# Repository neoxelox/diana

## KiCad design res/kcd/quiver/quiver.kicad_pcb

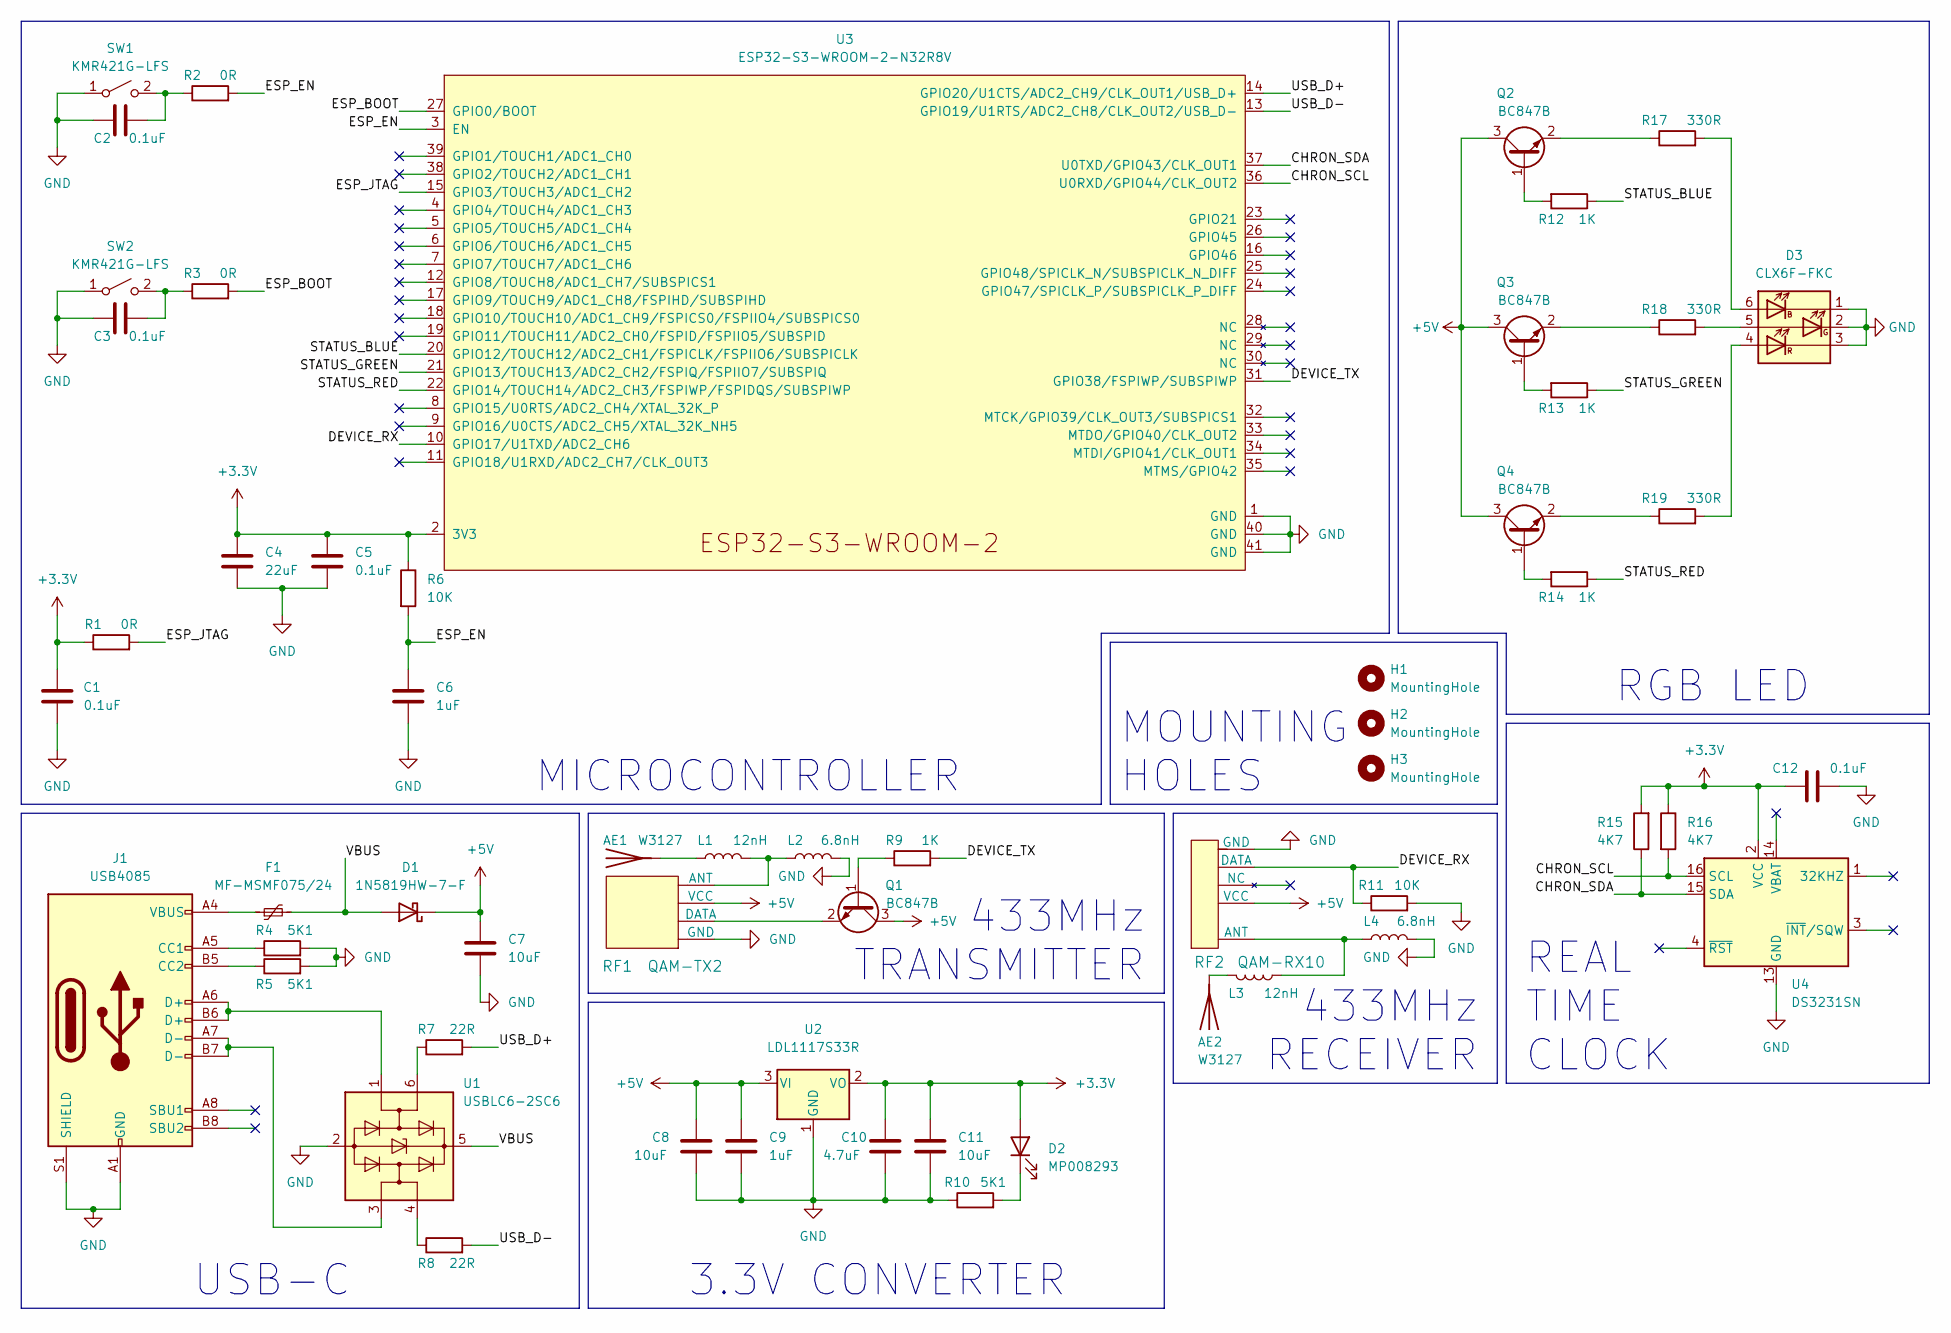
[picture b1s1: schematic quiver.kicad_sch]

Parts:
AE1, AE2: W3127
C1, C2, C3, C5, C12: 0.1uF; C_0805_2012Metric
C4: 22uF; C_0805_2012Metric
C6, C9: 1uF; C_0805_2012Metric
C7, C8, C11: 10uF; C_0805_2012Metric
C10: 4.7uF; C_0805_2012Metric
D1: 1N5819HW-7-F; D_SOD-123
D2: MP008293; LED_0805_2012Metric
D3: CLX6F-FKC
F1: MF-MSMF075/24; MF-MSMF075-24
H1, H2, H3: MountingHole; MountingHole_2.2mm_M2
J1: USB4085; GCT_USB4085
L1, L3: 12nH; L_0805_2012Metric
L2, L4: 6.8nH; L_0805_2012Metric
Q1, Q2, Q3, Q4: BC847B; SOT-23
R1, R2, R3: 0R; R_0805_2012Metric
R4, R5, R10: 5K1; R_0805_2012Metric
R6, R11: 10K; R_0805_2012Metric
R7, R8: 22R; R_0805_2012Metric
R9, R12, R13, R14: 1K; R_0805_2012Metric
R15, R16: 4K7; R_0805_2012Metric
R17, R18, R19: 330R; R_0805_2012Metric
RF1: QAM-TX2
RF2: QAM-RX10
SW1, SW2: KMR421G-LFS
U1: USBLC6-2SC6; SOT-23-6
U2: LDL1117S33R; SOT-223-3_TabPin2
U3: ESP32-S3-WROOM-2-N32R8V; ESP32-S3-WROOM-2
U4: DS3231SN; SOIC-16W_7.5x10.3mm_P1.27mm

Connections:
+3.3V: C1.2, C4.1, C5.1, C10.1, C11.1, C12.1, D2.2 (A), R1.1, R6.1, R15.2, R16.1, U2.2 (VO), U3.2 (3V3), U4.2 (VCC)
+5V: C7.1, C8.1, C9.1, D1.1 (K), Q1.3 (C), Q2.3 (C), Q3.3 (C), Q4.3 (C), RF1.3 (VCC), RF2.1 (VCC), U2.3 (VI)
/CHRON_SCL: R16.2, U3.36 (U0RXD/GPIO44/CLK_OUT2), U4.16 (SCL)
/CHRON_SDA: R15.1, U3.37 (U0TXD/GPIO43/CLK_OUT1), U4.15 (SDA)
/DEVICE_RX: R11.1, RF2.3 (DATA), U3.10 (GPIO17/U1TXD/ADC2_CH6)
/DEVICE_TX: R9.2, U3.31 (GPIO38/FSPIWP/SUBSPIWP)
/ESP_BOOT: R3.2, U3.27 (GPIO0/BOOT)
/ESP_EN: C6.1, R2.2, R6.2, U3.3 (EN)
/ESP_JTAG: R1.2, U3.15 (GPIO3/TOUCH3/ADC1_CH2)
/STATUS_BLUE: R12.1, U3.20 (GPIO12/TOUCH12/ADC2_CH1/FSPICLK/FSPIIO6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)
/STATUS_GREEN: R13.1, U3.21 (GPIO13/TOUCH13/ADC2_CH2/FSPIQ/FSPIIO7/S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)
/STATUS_RED: R14.1, U3.22 (GPIO14/TOUCH14/ADC2_CH3/FSPIWP/FSPIDQS/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)
/USB_D+: R7.2, U3.14 (GPIO20/U1CTS/ADC2_CH9/CLK_OUT1/USB_D+)
/USB_D-: R8.2, U3.13 (GPIO19/U1RTS/ADC2_CH8/CLK_OUT2/USB_D-)
/VBUS: D1.2 (A), F1.2, U1.5 (VBUS)
GND: C1.1, C2.1, C3.1, C4.2, C5.2, C6.2, C7.2, C8.2, C9.2, C10.2, C11.2, C12.2, D3.1 (BC), D3.2 (GC), D3.3 (RC), J1.A1 (GND), J1.A12 (GND), J1.B1 (GND), J1.B12 (GND), J1.S1 (SHIELD), L2.2, L4.2, R4.2, R5.2, R10.1, R11.2, RF1.1 (GND), RF2.4 (GND), SW1.1 (A), SW2.1 (A), U1.2 (GND), U2.1 (GND), U3.1 (GND), U3.40 (GND), U3.41 (GND), U4.5 (GND), U4.6 (GND), U4.7 (GND), U4.8 (GND), U4.9 (GND), U4.10 (GND), U4.11 (GND), U4.12 (GND), U4.13 (GND)
unnamed: AE1.1 (A), L1.1
unnamed: AE2.1 (A), L3.2
unnamed: C2.2, R2.1, SW1.2 (B)
unnamed: C3.2, R3.1, SW2.2 (B)
unnamed: D2.1 (K), R10.2
unnamed: D3.4 (RA), R19.2
unnamed: D3.5 (GA), R18.2
unnamed: D3.6 (BA), R17.2
unnamed: F1.1, J1.A4 (VBUS), J1.A9 (VBUS), J1.B4 (VBUS), J1.B9 (VBUS)
unnamed: J1.A5 (CC1), R4.1
unnamed: J1.A6 (D+), J1.B6 (D+), U1.1 (I/O1)
unnamed: J1.A7 (D-), J1.B7 (D-), U1.3 (I/O2)
unnamed: J1.B5 (CC2), R5.1
unnamed: L1.2, L2.1, RF1.4 (ANT)
unnamed: L3.1, L4.1, RF2.5 (ANT)
unnamed: Q1.1 (B), R9.1
unnamed: Q1.2 (E), RF1.2 (DATA)
unnamed: Q2.1 (B), R12.2
unnamed: Q2.2 (E), R17.1
unnamed: Q3.1 (B), R13.2
unnamed: Q3.2 (E), R18.1
unnamed: Q4.1 (B), R14.2
unnamed: Q4.2 (E), R19.1
unnamed: R7.1, U1.6 (I/O1)
unnamed: R8.1, U1.4 (I/O2)

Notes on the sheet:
USB-C
MICROCONTROLLER
MOUNTING HOLES
RGB LED
REAL TIME CLOCK
433MHz RECEIVER
433MHz TRANSMITTER
3.3V CONVERTER

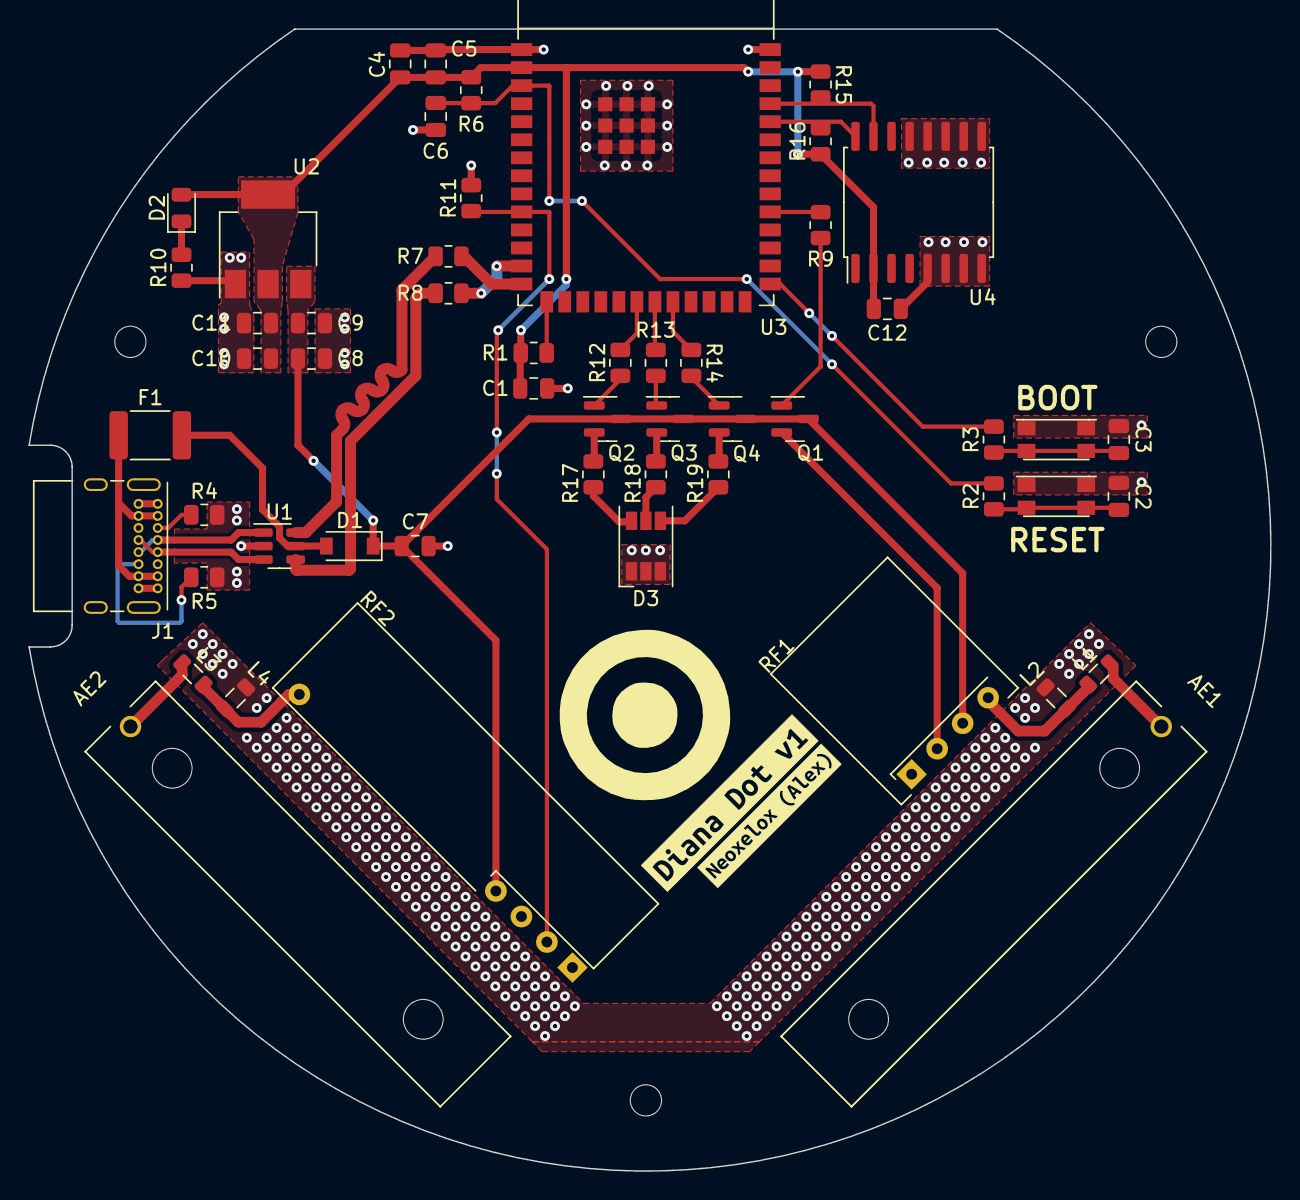
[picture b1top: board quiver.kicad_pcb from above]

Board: 2 copper layers, 87.4 x 80.4 mm, 60 parts (1 on the bottom side), 41 nets.

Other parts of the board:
kibuzzard-6373EA89: G***; kibuzzard-6373EA89
kibuzzard-6373EB20: G***; kibuzzard-6373EB20
kibuzzard-6373EBEE: G***; kibuzzard-6373EBEE

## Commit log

2023-01-26 Init documentation and resources
2023-01-26 Add backend and frontend sources submodules
2023-01-26 Add Bachelor's Thesis documents
2023-11-18 Bump bow version
2023-11-21 Bumb bow version
2023-11-27 Update arrow and bow
